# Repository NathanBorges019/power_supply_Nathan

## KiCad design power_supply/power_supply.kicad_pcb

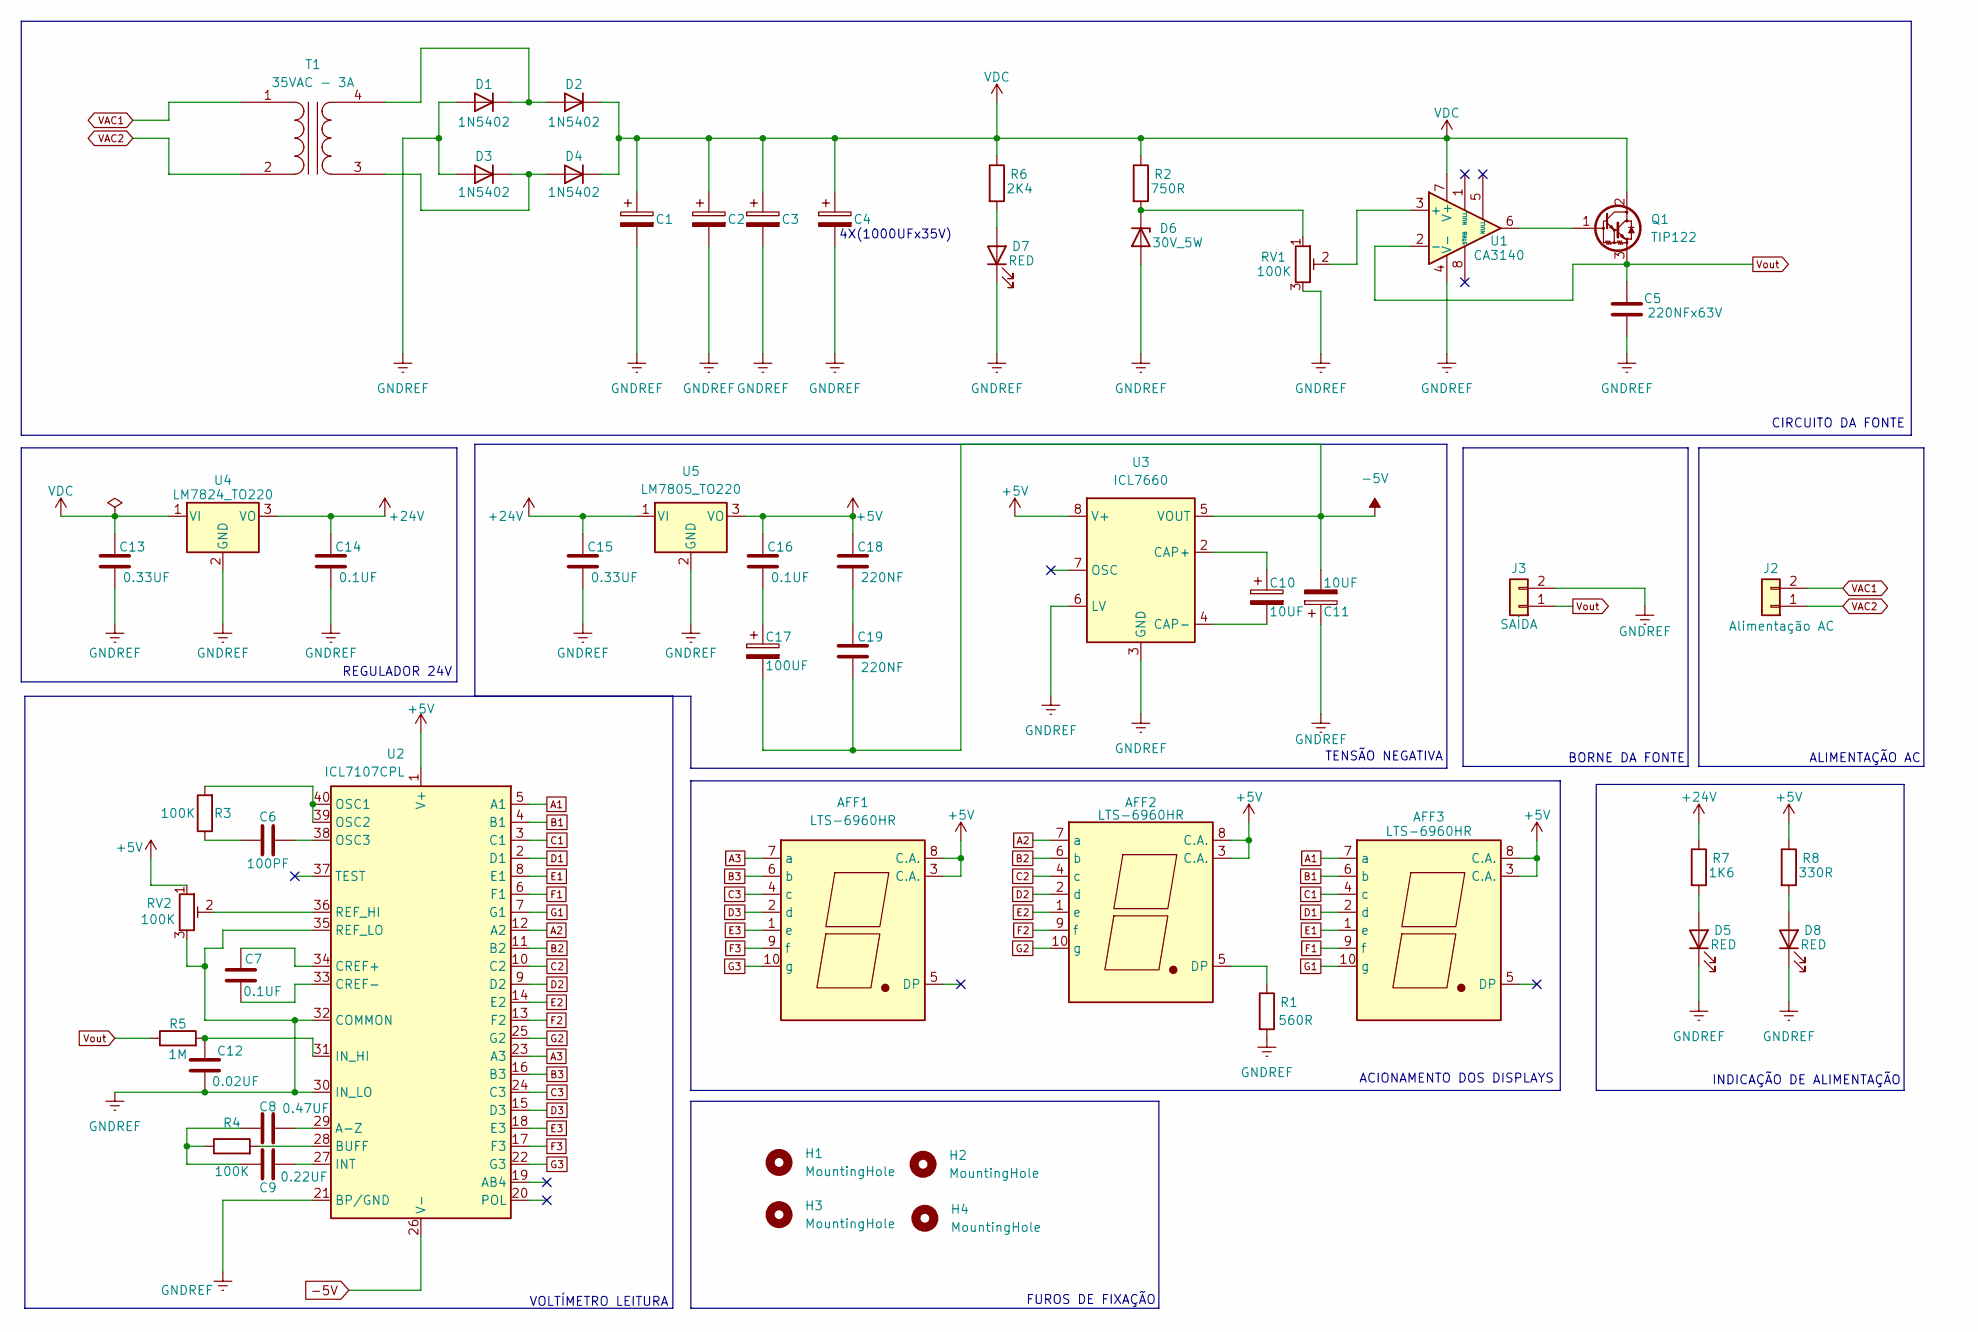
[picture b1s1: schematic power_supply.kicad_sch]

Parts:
AFF1: LTS-6960HR; TestPoint_Pad_D2.0mm
AFF2, AFF3: LTS-6960HR; 7SegmentLED_LTS6760_LTS6780
C1, C2, C3, C4: 1000UFx50V; CP_Elec_16x17.5
C5: 220NFx63V; C_1206_3216Metric
C6: 100PF; C_1206_3216Metric
C7, C14, C16: 0.1UF; C_1206_3216Metric
C8: 0.47UF; C_1206_3216Metric
C9: 0.22UF; C_1206_3216Metric
C10, C11: 10UF; CP_Elec_5x5.4
C12: 0.02UF; C_1206_3216Metric
C13, C15: 0.33UF; C_1206_3216Metric
C17: 100UF; CP_Elec_6.3x7.7
C18, C19: 220NF; C_1206_3216Metric
D1, D2, D3, D4: 1N5402; D_DO-201AD_P15.24mm_Horizontal
D5, D7, D8: RED; LED_1206_3216Metric
D6: 30V_5W; D_SMA
H1, H2, H3, H4: MountingHole; MountingHole_3.2mm_M3
J2: Alimentação AC; Molex_KK-396_5273-02A_1x02_P3.96mm_Vertical
J3: SAÍDA; Molex_KK-396_5273-02A_1x02_P3.96mm_Vertical
Q1: TIP122; TO-220-3_Vertical
R1: 560R; R_1206_3216Metric
R2: 750R; R_1206_3216Metric
R3, R4: 100K; R_1206_3216Metric
R5: 1M; R_1206_3216Metric
R6: 2K4; R_1206_3216Metric
R7: 1K6; R_1206_3216Metric
R8: 330R; R_1206_3216Metric
RV1: 100K; Potentiometer_Vishay_248GJ-249GJ_Single_Horizontal
RV2: 100K; Potentiometer_Vishay_T73YP_Vertical
T1: 35VAC - 3A; Molex_KK-396_5273-04A_1x04_P3.96mm_Vertical
U1: CA3140; SOIC-8_3.9x4.9mm_P1.27mm
U2: ICL7107CPL; DIP-40_W15.24mm
U3: ICL7660; SOIC-8_3.9x4.9mm_P1.27mm
U4: LM7824_TO220; TO-220-3_Horizontal_TabDown
U5: LM7805_TO220; TO-220-3_Horizontal_TabDown

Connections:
+5V: AFF1.3 (C.A.), AFF1.8 (C.A.), AFF2.3 (C.A.), AFF2.8 (C.A.), AFF3.3 (C.A.), AFF3.8 (C.A.), C16.1, C18.1, R8.1, RV2.1, U2.1 (V+), U3.8 (V+), U5.3 (VO)
+24V: C14.1, C15.1, R7.1, U4.3 (VO), U5.1 (VI)
-5V: C11.2, C17.2, C19.2, U2.26 (V-), U3.5 (VOUT)
A1: AFF3.7 (a), U2.5 (A1)
A2: AFF2.7 (a), U2.12 (A2)
A3: AFF1.7 (a), U2.23 (A3)
B1: AFF3.6 (b), U2.4 (B1)
B2: AFF2.6 (b), U2.11 (B2)
B3: AFF1.6 (b), U2.16 (B3)
C1: AFF3.4 (c), U2.3 (C1)
C2: AFF2.4 (c), U2.10 (C2)
C3: AFF1.4 (c), U2.24 (C3)
D1: AFF3.2 (d), U2.2 (D1)
D2: AFF2.2 (d), U2.9 (D2)
D3: AFF1.2 (d), U2.15 (D3)
E1: AFF3.1 (e), U2.8 (E1)
E2: AFF2.1 (e), U2.14 (E2)
E3: AFF1.1 (e), U2.18 (E3)
F1: AFF3.9 (f), U2.6 (F1)
F2: AFF2.9 (f), U2.13 (F2)
F3: AFF1.9 (f), U2.17 (F3)
G1: AFF3.10 (g), U2.7 (G1)
G2: AFF2.10 (g), U2.25 (G2)
G3: AFF1.10 (g), U2.22 (G3)
GNDREF: C1.2, C2.2, C3.2, C4.2, C5.2, C11.1, C12.2, C13.2, C14.2, C15.2, D1.2 (A), D3.2 (A), D5.1 (K), D6.2 (A), D7.1 (K), D8.1 (K), J3.2, R1.2, RV1.3, RV2.3, U1.4 (V-), U2.21 (BP/GND), U2.30 (IN_LO), U2.32 (COMMON), U2.35 (REF_LO), U3.3 (GND), U3.6 (LV), U4.2 (GND), U5.2 (GND)
unnamed: AFF2.5 (DP), R1.1
unnamed: C6.2, R3.1
unnamed: C8.1, C9.1, R4.1
unnamed: C16.2, C17.1
unnamed: C18.2, C19.1
unnamed: D1.1 (K), D2.2 (A), T1.4 (SB)
unnamed: D3.1 (K), D4.2 (A), T1.3 (SA)
unnamed: D5.2 (A), R7.2
unnamed: D6.1 (K), R2.2, RV1.1
unnamed: D7.2 (A), R6.2
unnamed: D8.2 (A), R8.2
unnamed: Q1.1 (B), U1.6
unnamed: RV1.2, U1.3 (+)
unnamed: C8.2, U2.29 (A-Z)
unnamed: R4.2, U2.28 (BUFF)
unnamed: C7.1, U2.34 (CREF+)
unnamed: C7.2, U2.33 (CREF-)
unnamed: C9.2, U2.27 (INT)
unnamed: C12.1, R5.2, U2.31 (IN_HI)
unnamed: R3.2, U2.39 (OSC2), U2.40 (OSC1)
unnamed: C6.1, U2.38 (OSC3)
unnamed: RV2.2, U2.36 (REF_HI)
unnamed: C10.1, U3.2 (CAP+)
unnamed: C10.2, U3.4 (CAP-)
VAC1: J2.2, T1.1 (AA)
VAC2: J2.1, T1.2 (AB)
VDC: C1.1, C2.1, C3.1, C4.1, C13.1, D2.1 (K), D4.1 (K), Q1.2 (C), R2.1, R6.1, U1.7 (V+), U4.1 (VI)
Vout: C5.1, J3.1, Q1.3 (E), R5.1, U1.2 (-)

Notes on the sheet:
TENSÃO NEGATIVA
VOLTÍMETRO LEITURA
CIRCUITO DA FONTE
INDICAÇÃO DE ALIMENTAÇÃO
4X(1000UFx35V)
REGULADOR 24V
BORNE DA FONTE
ALIMENTAÇÃO AC
FUROS DE FIXAÇÃO
ACIONAMENTO DOS DISPLAYS

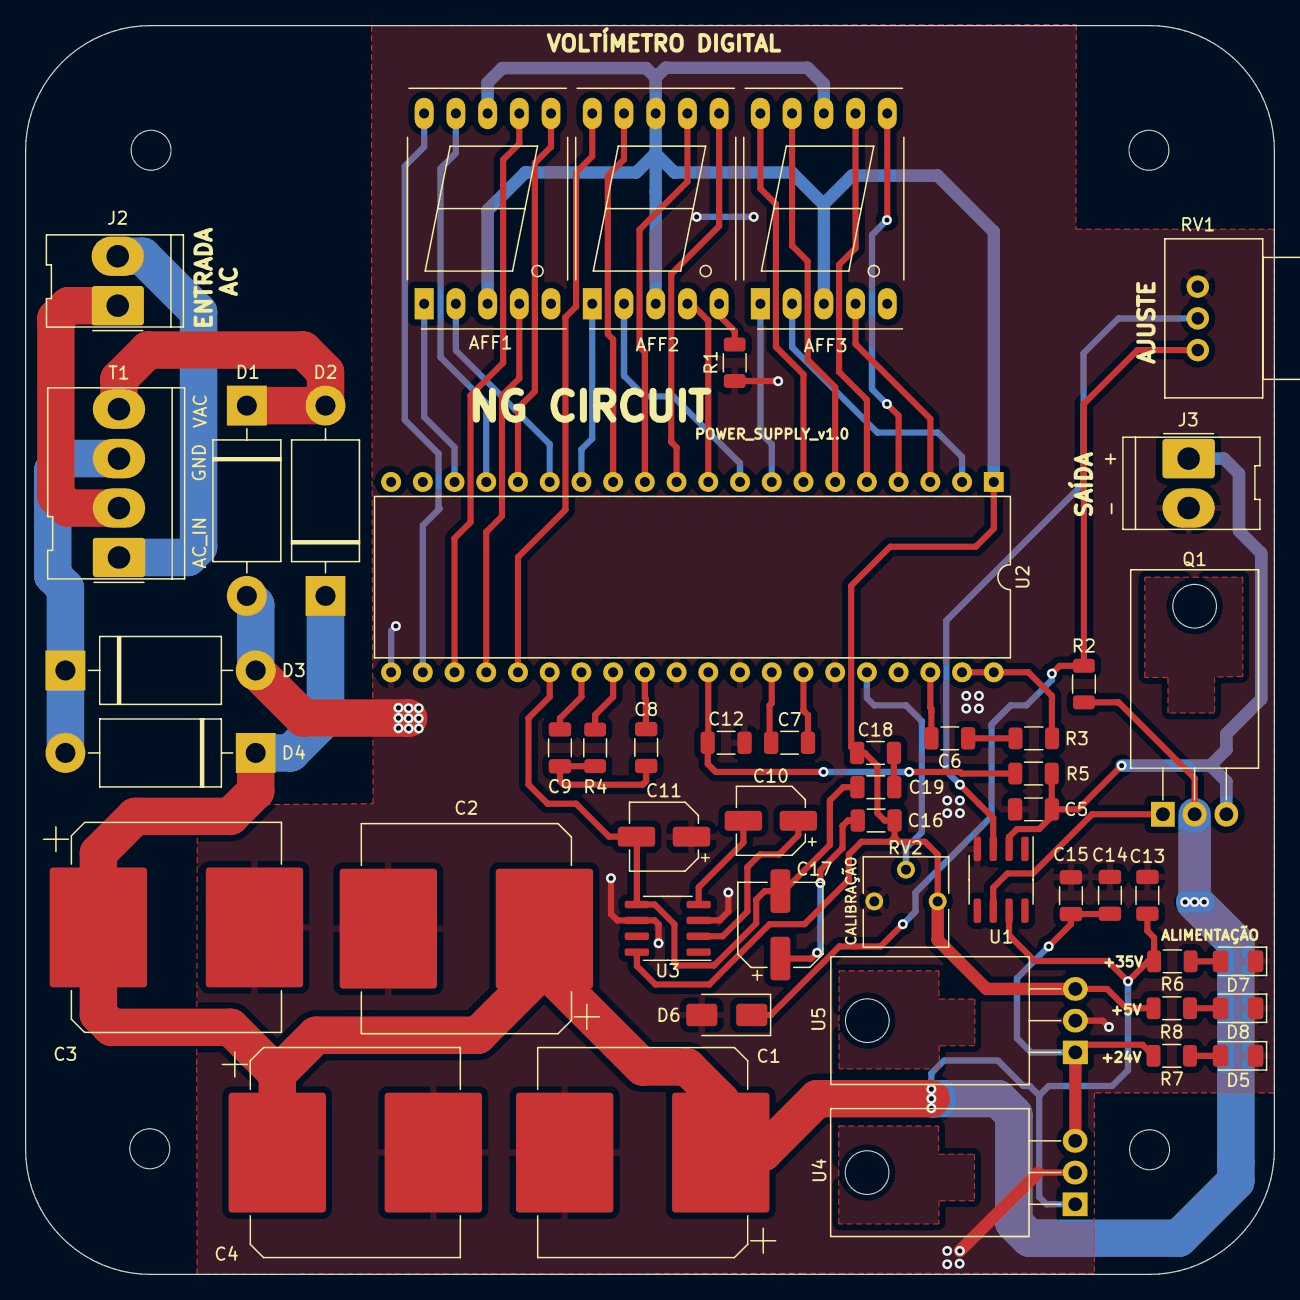
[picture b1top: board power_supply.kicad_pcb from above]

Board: 2 copper layers, 100.0 x 100.0 mm, 53 parts (0 on the bottom side), 53 nets.

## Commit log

2023-09-16 primeiro commit
2023-09-16 Circuito do Transformador + especificações iniciais
2023-09-23 Considerações Finais - Circuito da fonte + Amplificador
2023-10-29 Adicionado o circuito dos reguladores de tensão, bem como o circuito do ICL para controle do voltímetro via display de 7 segmentos.
2023-11-02 Finalização do esquemático, seleção de footprints e organização dos componentes no layout
2023-11-05 Retira do Transformador On-Board para externo, troca de footprint para um conector Molex de 4 vias (3.96mm); Início do roteamento das trilhas e isolação dos planos GND.
2023-11-11 Finalização do Layout, aguardando dúvida das Vias para trilhas de 3mm.
2023-11-17 Finalização/Correção do Layout solicitado!
2023-11-18 Atualização de Trilhas e adicionado fotos do 3D atualizado
